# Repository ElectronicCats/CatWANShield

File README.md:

# CatWAN Arduino LoRa Shield

<p align="center">
    
</p>

<p align=center>

</p>

With the CatWAN Arduino LoRa Shield, you will be able to unlock the power of LoRa technology for long-range, low-power communication in an Arduino UNO. Seamlessly integrate your Arduino UNO into LoRaWAN networks for a variety of applications.

This repository contains the KiCad files for a LoRa shield for Arduino Uno and some examples that may help you to get running your LoRa-based applications with the power of an Arduino UNO 

- The folder named "LoRA_PHY_RH" refers to the communication
P2P by the Physical layer of LoRa, in here you can find 2 examples one as the Transmitter (Which also  is capable of receiving information) and the second as the receiver (Which also is capable of transmitting information), both examples work with the [RadioHead](http://www.airspayce.com/mikem/arduino/RadioHead/) library  

- The folder named "LoRA_PHY" refers to the communication
P2P by the Physical layer of LoRa, in here you can find 2 examples one as the Transmitter and the second as the receiver, both examples work with the Official [LoRa](https://github.com/sandeepmistry/arduino-LoRa) library from Arduino.

- The folder named LoRa_WAN refers to the communication by a LoRaWAN network from your device to the internet, by the two methods that exist OTAA and ABP, both examples were created to read a GPS or/and temperature from one analogic sensor attached to the analog input.

Electronic Cats invests time and resources in providing this open-source design, please support Electronic Cats and open-source hardware by purchasing products from Electronic Cats!

Designed by Electronic Cats.

## How to contribute 
 Contributions are welcome! 

Please read the document  [**Contribution Manual**](https://github.com/ElectronicCats/electroniccats-cla/blob/main/electroniccats-contribution-manual.md)  which will show you how to contribute your changes to the project.

✨ Thanks to all our [contributors](https://github.com/ElectronicCats/Cat-Sink/graphs/contributors)! ✨

See [**_Electronic Cats CLA_**](https://github.com/ElectronicCats/electroniccats-cla/blob/main/electroniccats-cla.md) for more information.

See the  [**community code of conduct**](https://github.com/ElectronicCats/electroniccats-cla/blob/main/electroniccats-community-code-of-conduct.md) for a vision of the community we want to build and what we expect from it."			

# License

Firmware released under a GNU AGPL v3.0 license. See the LICENSE file for more information.

Hardware released under a CERN Open Hardware Licence v1.2. See the LICENSE_HARDWARE file for more information.

Electronic Cats is a registered trademark, please do not use it if you sell these PCBs.

5 Jul 2018

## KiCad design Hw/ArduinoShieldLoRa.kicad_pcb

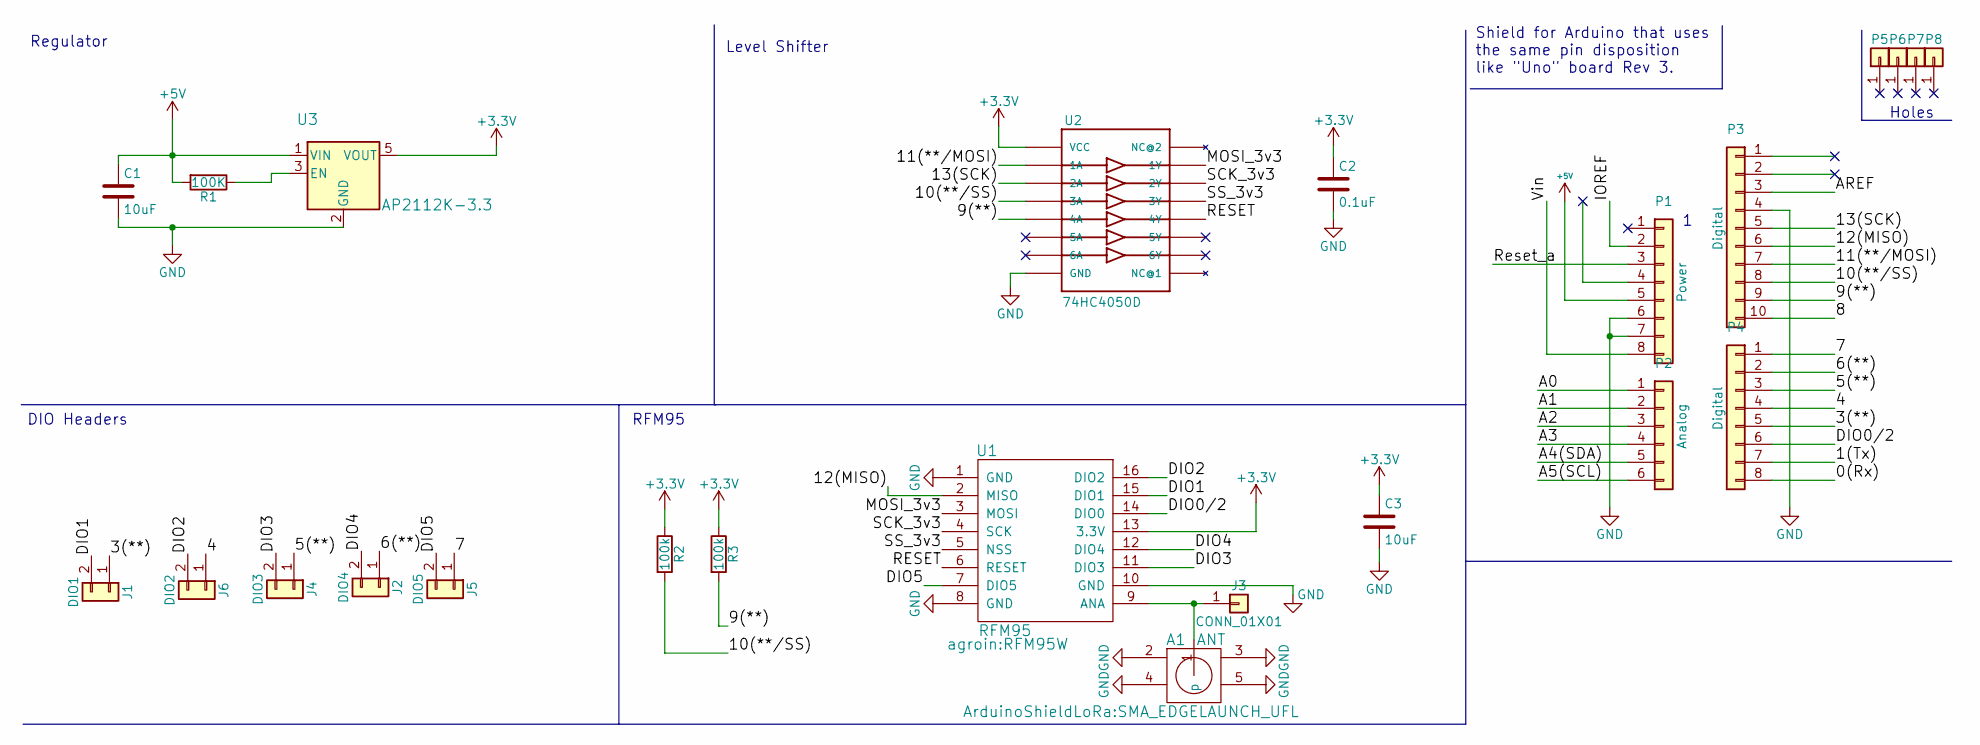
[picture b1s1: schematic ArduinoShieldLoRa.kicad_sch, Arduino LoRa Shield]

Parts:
A1: ANT; SMA_EDGELAUNCH_UFL
C1, C3: 10uF; C_0805_HandSoldering
C2: 0.1uF; C_0805_HandSoldering
J1: DIO1; Pin_Header_Straight_1x02_Pitch2.54mm
J2: DIO4; Pin_Header_Straight_1x02_Pitch2.54mm
J3: CONN_01X01; SolderWirePad_single_0-8mmDrill
J4: DIO3; Pin_Header_Straight_1x02_Pitch2.54mm
J5: DIO5; Pin_Header_Straight_1x02_Pitch2.54mm
J6: DIO2; Pin_Header_Straight_1x02_Pitch2.54mm
P1: Power; Socket_Strip_Arduino_1x08
P2: Analog; Socket_Strip_Arduino_1x06
P3: Digital; Socket_Strip_Arduino_1x10
P4: Digital; Socket_Strip_Arduino_1x08
P5, P6, P7, P8: CONN_01X01; Arduino_1pin
R1: 100K; R_0805_HandSoldering
R2, R3: 100k; R_0805_HandSoldering
U1: RFM95; RFM95W
U2: 74HC4050D; SO16
U3: AP2112K-3.3; SOT-23-5

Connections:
+3V3: C2.1, C3.1, R2.1, R3.1, U1.13 (3.3V), U2.1 (VCC), U3.5 (VOUT)
/0(Rx): P4.8
/1(Tx): P4.7
/3(**): J1.1, P4.5
/4: J6.1, P4.4
/5(**): J4.1, P4.3
/6(**): J2.1, P4.2
/7: J5.1, P4.1
/8: P3.10
/9(**): P3.9, R3.2, U2.9 (4A)
/10(**/SS): P3.8, R2.2, U2.7 (3A)
/11(**/MOSI): P3.7, U2.3 (1A)
/12(MISO): P3.6, U1.2 (MISO)
/13(SCK): P3.5, U2.5 (2A)
/A0: P2.1
/A1: P2.2
/A2: P2.3
/A3: P2.4
/A4(SDA): P2.5
/A5(SCL): P2.6
/AREF: P3.3
/DIO0/2: P4.6, U1.14 (DIO0)
/DIO1: J1.2, U1.15 (DIO1)
/DIO2: J6.2, U1.16 (DIO2)
/DIO3: J4.2, U1.11 (DIO3)
/DIO4: J2.2, U1.12 (DIO4)
/DIO5: J5.2, U1.7 (DIO5)
/IOREF: P1.2
/MOSI_3v3: U1.3 (MOSI), U2.2 (1Y)
/RESET: U1.6 (RESET), U2.10 (4Y)
/Reset_a: P1.3
/SCK_3v3: U1.4 (SCK), U2.4 (2Y)
/SS_3v3: U1.5 (NSS), U2.6 (3Y)
/Vin: P1.8
GND: A1.2, A1.3, A1.4, A1.5, C1.2, C2.2, C3.2, P1.6, P1.7, P3.4, U1.1 (GND), U1.8 (GND), U1.10 (GND), U2.8 (GND), U3.2 (GND)
unnamed: A1.1 (p), J3.1, U1.9 (ANA)
unnamed: R1.1, U3.3 (EN)

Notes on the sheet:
DIO Headers
RFM95
Shield for Arduino that uses the same pin disposition like "Uno" board Rev 3.
Level Shifter
Holes
Regulator

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
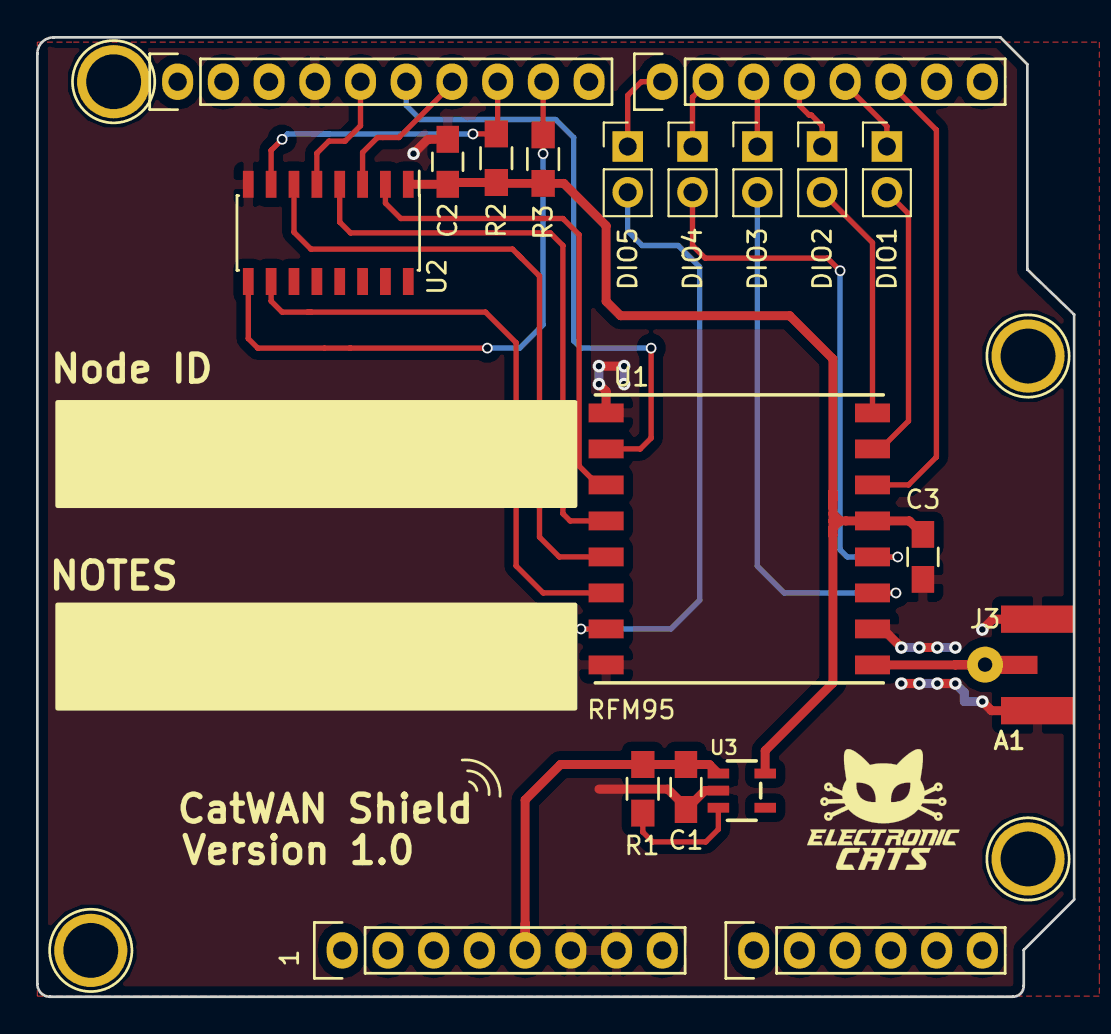
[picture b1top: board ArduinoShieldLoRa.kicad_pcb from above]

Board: 2 copper layers, 57.6 x 53.3 mm, 25 parts (1 on the bottom side), 25 nets.

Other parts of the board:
svg2mod: electronic; titule_electronic_med

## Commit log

2017-06-14 Add project
2017-06-14 Add resistors
2017-06-14 Fix RFM95
2017-06-14 finished
2017-06-14 add pin for cable as antenna
2017-06-14 Added logos
2017-06-14 Gerber config
2017-11-15 add gitignore
2017-11-15 Add examples
2017-11-15 Update README with logo Tindie
2018-05-23 update library
2018-05-23 Added PDF
2018-07-06 Update folder for KiCad project
2018-07-06 Update examples with RadioHead library
2018-07-06 Add Arduino LoRa Library
2018-07-25 Update gitignore
2018-07-25 Manita de gato CatWAN shield
2018-07-25 Update update PDF
2018-07-25 Update sch
2018-07-25 data place
2023-12-22 Format updated
    The readme format has been updated
2023-12-22 License image resizing
2024-04-11 feat(docs):Update README.md
    Add how to contribute
